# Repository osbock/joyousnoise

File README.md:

# joyousnoise
Small analog synth based on Schmitt trigger inverter

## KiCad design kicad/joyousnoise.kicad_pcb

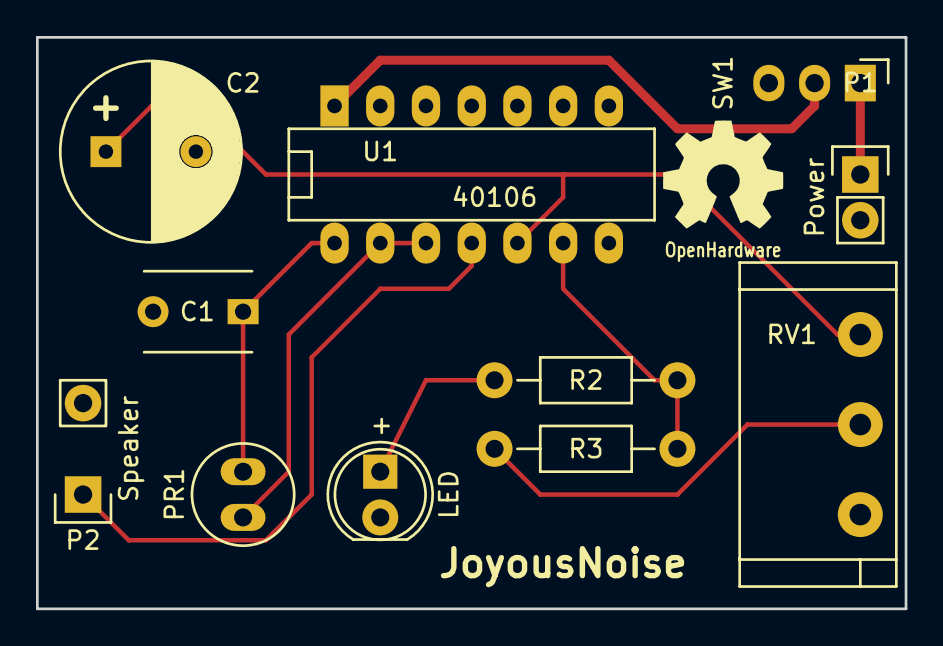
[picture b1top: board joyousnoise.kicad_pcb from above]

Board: 2 copper layers, 48.3 x 31.8 mm, 11 parts (0 on the bottom side), 10 nets.

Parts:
C1: C; C_Disc_D6_P5
C2: CP; C_Radial_D10_L20_P5
D1: LED; LED-5MM
P1: Power; Pin_Header_Straight_1x02
P2: Speaker; Speaker_conn
PR1: Photores; PhotoResistor
R2, R3: R; Resistor_Horizontal_RM10mm
RV1: POT; Potentiometer_Alps-RK16-single
SW1: SPST; SM_SlideSW
U1: 40106; DIP-14__300_ELL

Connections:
/OUT: P2.1, U1.4
GND: C1.2, C2.2, D1.1, P1.2, P2.2, U1.7
unnamed: C1.1, PR1.2, U1.1
unnamed: C2.1, RV1.1, U1.5
unnamed: D1.2, R2.1
unnamed: P1.1, SW1.1
unnamed: PR1.1, U1.2, U1.3
unnamed: R2.2, R3.2, U1.6
unnamed: R3.1, RV1.2
VCC: SW1.2, U1.14

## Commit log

2015-09-23 fix up some footprints for easier assembly, clean up tracks
2015-09-23 add gerbers
2015-09-23 add lib.pretty
2015-09-23 redo lost work, add power switch
2015-09-23 update footprints
2015-09-23 update schema library
2016-01-23 update silkscreen
2021-02-06 update for kicad version stuff
